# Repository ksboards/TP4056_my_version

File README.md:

Battery charging and protection pcb and schematic using kicad

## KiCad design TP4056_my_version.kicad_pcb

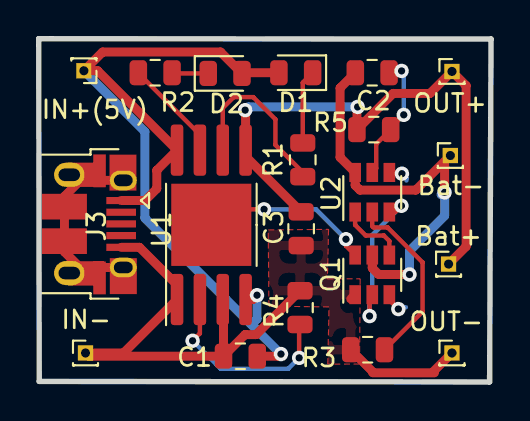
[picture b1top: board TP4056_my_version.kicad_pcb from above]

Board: 2 copper layers, 25.1 x 19.1 mm, 20 parts (0 on the bottom side), 13 nets.

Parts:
Bat+: Conn_01x01; PinHeader_1x01_P1.00mm_Vertical
Bat-: Conn_01x01; PinHeader_1x01_P1.00mm_Vertical
C1, C2, C3: C; C_0805_2012Metric
D1, D2: LED; LED_0805_2012Metric
IN+(5V): Conn_01x01; PinHeader_1x01_P1.00mm_Vertical
IN-: Conn_01x01; PinHeader_1x01_P1.00mm_Vertical
J3: USB_B_Micro; USB_Micro-B_Amphenol_10103594-0001LF_Horizontal
OUT+: Conn_01x01; PinHeader_1x01_P1.00mm_Vertical
OUT-: Conn_01x01; PinHeader_1x01_P1.00mm_Vertical
Q1: FS8205; SOT-23-6
R1, R2, R3, R4, R5: R; R_0805_2012Metric
U1: TP4056; SOP-8-1EP_4.57x4.57mm_P1.27mm_EP4.57x4.45mm
U2: DW01A; SOT-23-6

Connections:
GND: C1.2, C3.2, IN-.1, J3.5, OUT-.1, Q1.1, R3.2, R4.1, U1.1, U1.3
unnamed: Bat+.1, C3.1, OUT+.1, R5.1, U1.5
unnamed: Bat-.1, C2.1, Q1.5, U2.6
unnamed: C1.1, D1.2, D2.2, IN+(5V).1, J3.1, U1.4, U1.8
unnamed: C2.2, R5.2, U2.5
unnamed: D1.1, R1.2
unnamed: D2.1, R2.2
unnamed: Q1.2, U2.3
unnamed: Q1.4, U2.1
unnamed: R1.1, U1.6
unnamed: R2.1, U1.7
unnamed: R3.1, U2.2
unnamed: R4.2, U1.2

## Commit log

2020-11-02 3D_view
